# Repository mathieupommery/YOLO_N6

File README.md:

# Edge AI Vision Board (STM32N657)

This repository contains the design files for a high-performance, low-power Edge AI development board centered around the STM32N657 microcontroller. This project serves as a preliminary test platform for implementing high-speed differential and parallel buses (MIPI CSI-2 and Octo-SPI) in a compact form factor.

The primary objective is to execute YOLO-based object detection models efficiently, with data output and control interfacing managed via UART.

## Hardware Overview

### Board Images

| Front View | Back View |
| :--- | :--- |
|||

### Core Components

* **MCU:** STM32N657IO (High-performance Arm Cortex-M7 with integrated NPU)
* **External Memory (PSRAM):** 64MB Octo-SPI DTR (running at 200MHz)
* **External Storage (Flash):** 256MB Octo-SPI
    * *Note: PSRAM and Flash are multiplexed on a HyperBus and connected via a daisy-chain topology.*

### Peripherals & Connectivity

* **Camera:** MIPI CSI connector, pin-compatible with the Raspberry Pi 5 camera.
* **Display:** Integrated ST7789 SPI display.
* **Storage:** MicroSD card connector, supporting up to 50MHz mode.
* **Debug:** Dedicated debug connector.
* **Data & Power:** USB-C connector.
* **Communication:** UART connector.

## Design Details & Constraints

This design was simulated using IBIS models to ensure signal integrity across all high-speed interfaces.

### Signal Integrity Metrics

* **MIPI CSI-2:**
    * Inter-pair skew: Matched to ±30ps.
    * Intra-pair skew: Matched to <0.1ps.
* **Octo-SPI:**
    * MCU to PSRAM : 8ps skew tolerance.
    * MCU to Flash : 70ps skew tolerance.
* **Layout:** The "3H rule" was strictly implemented throughout the entire board layout, including between meandering differential pairs, to minimize crosstalk.

## Project Roadmap

This project is a stepping stone towards developing more complex hardware. Following successful verification of this prototype, the next iteration is planned to feature LPDDR4 memory integrated with an STM32MP257F MPU in a similar form factor.

---

**Contact:** [Pommery Mathieu]

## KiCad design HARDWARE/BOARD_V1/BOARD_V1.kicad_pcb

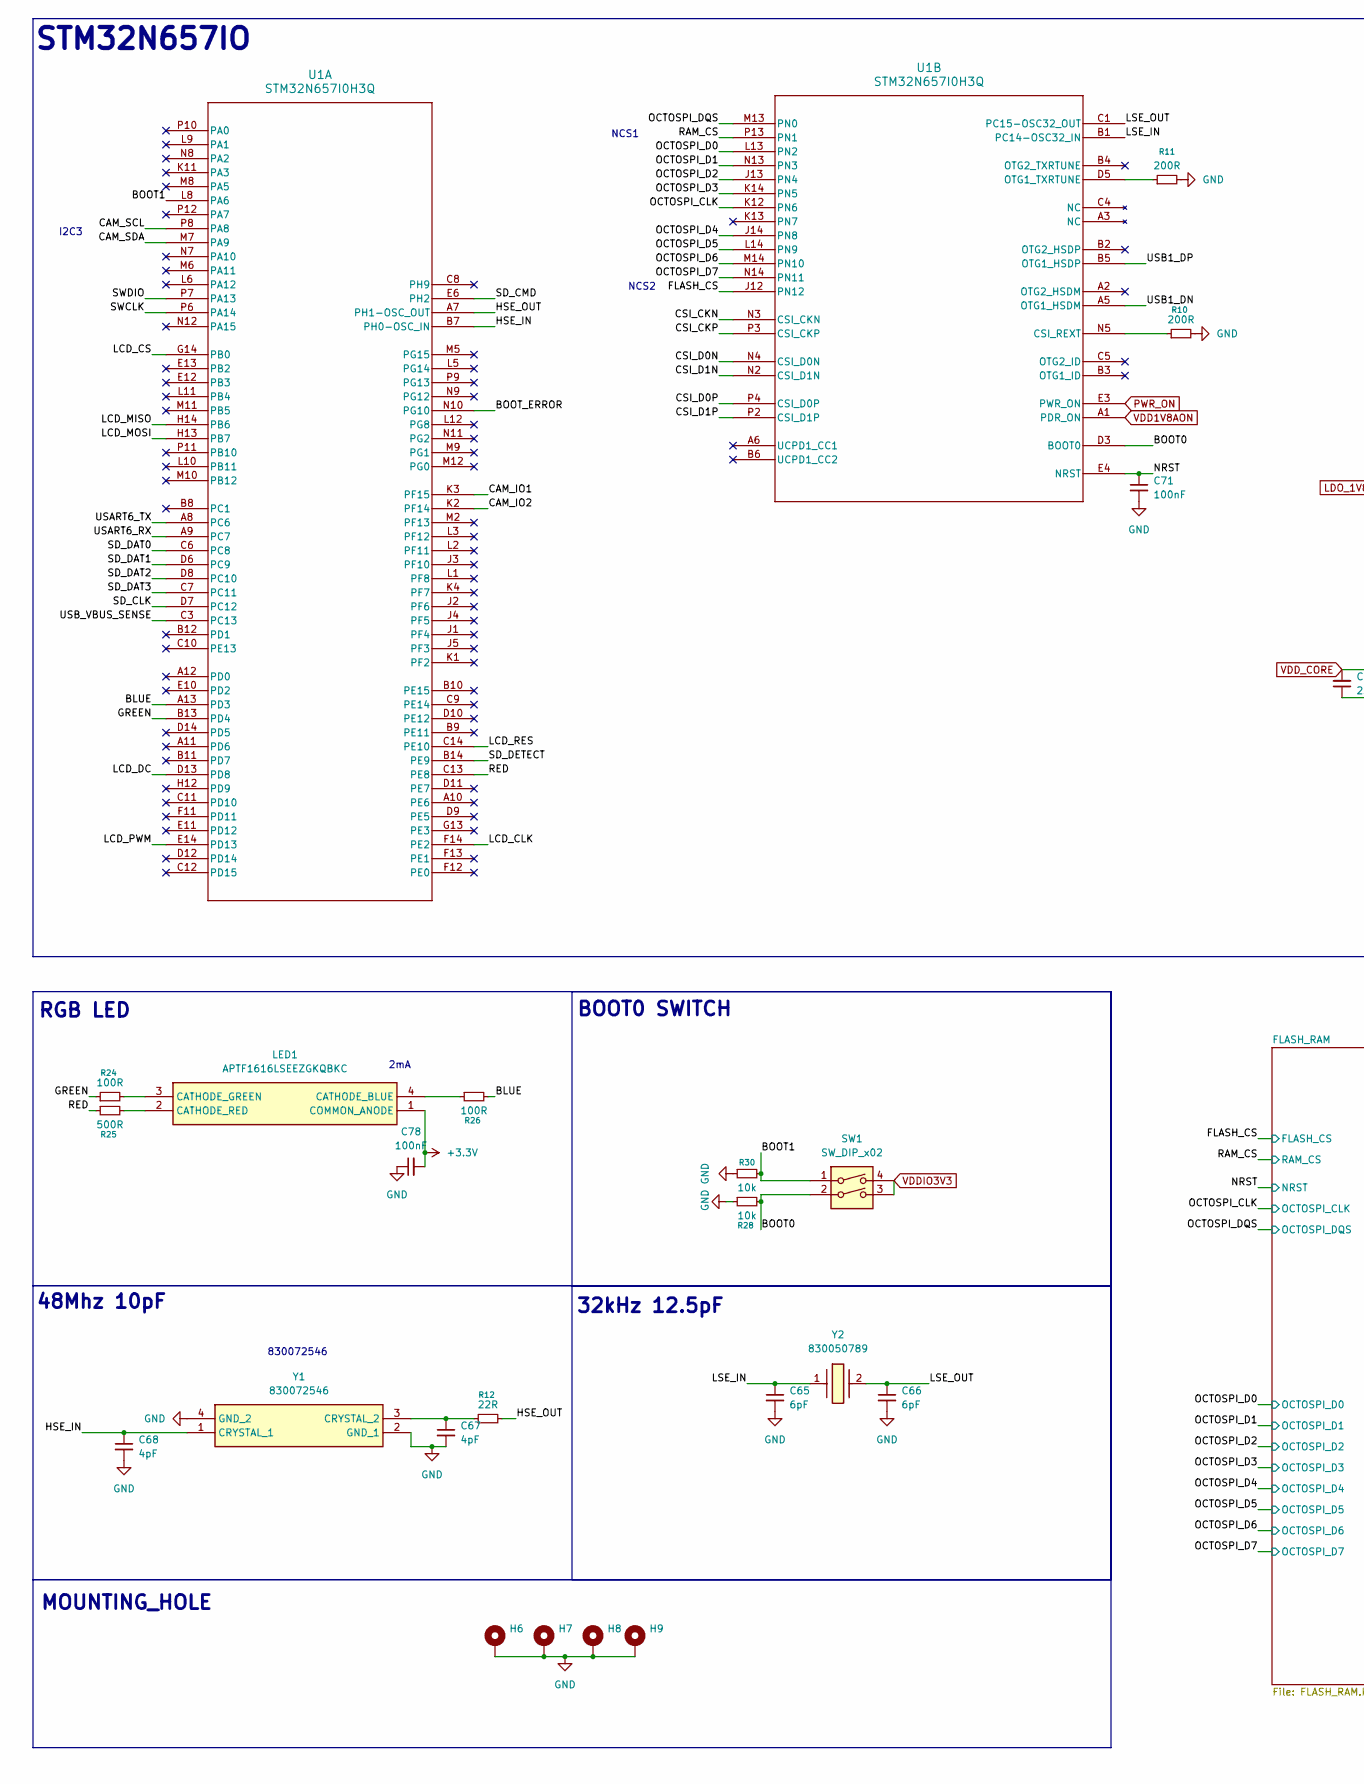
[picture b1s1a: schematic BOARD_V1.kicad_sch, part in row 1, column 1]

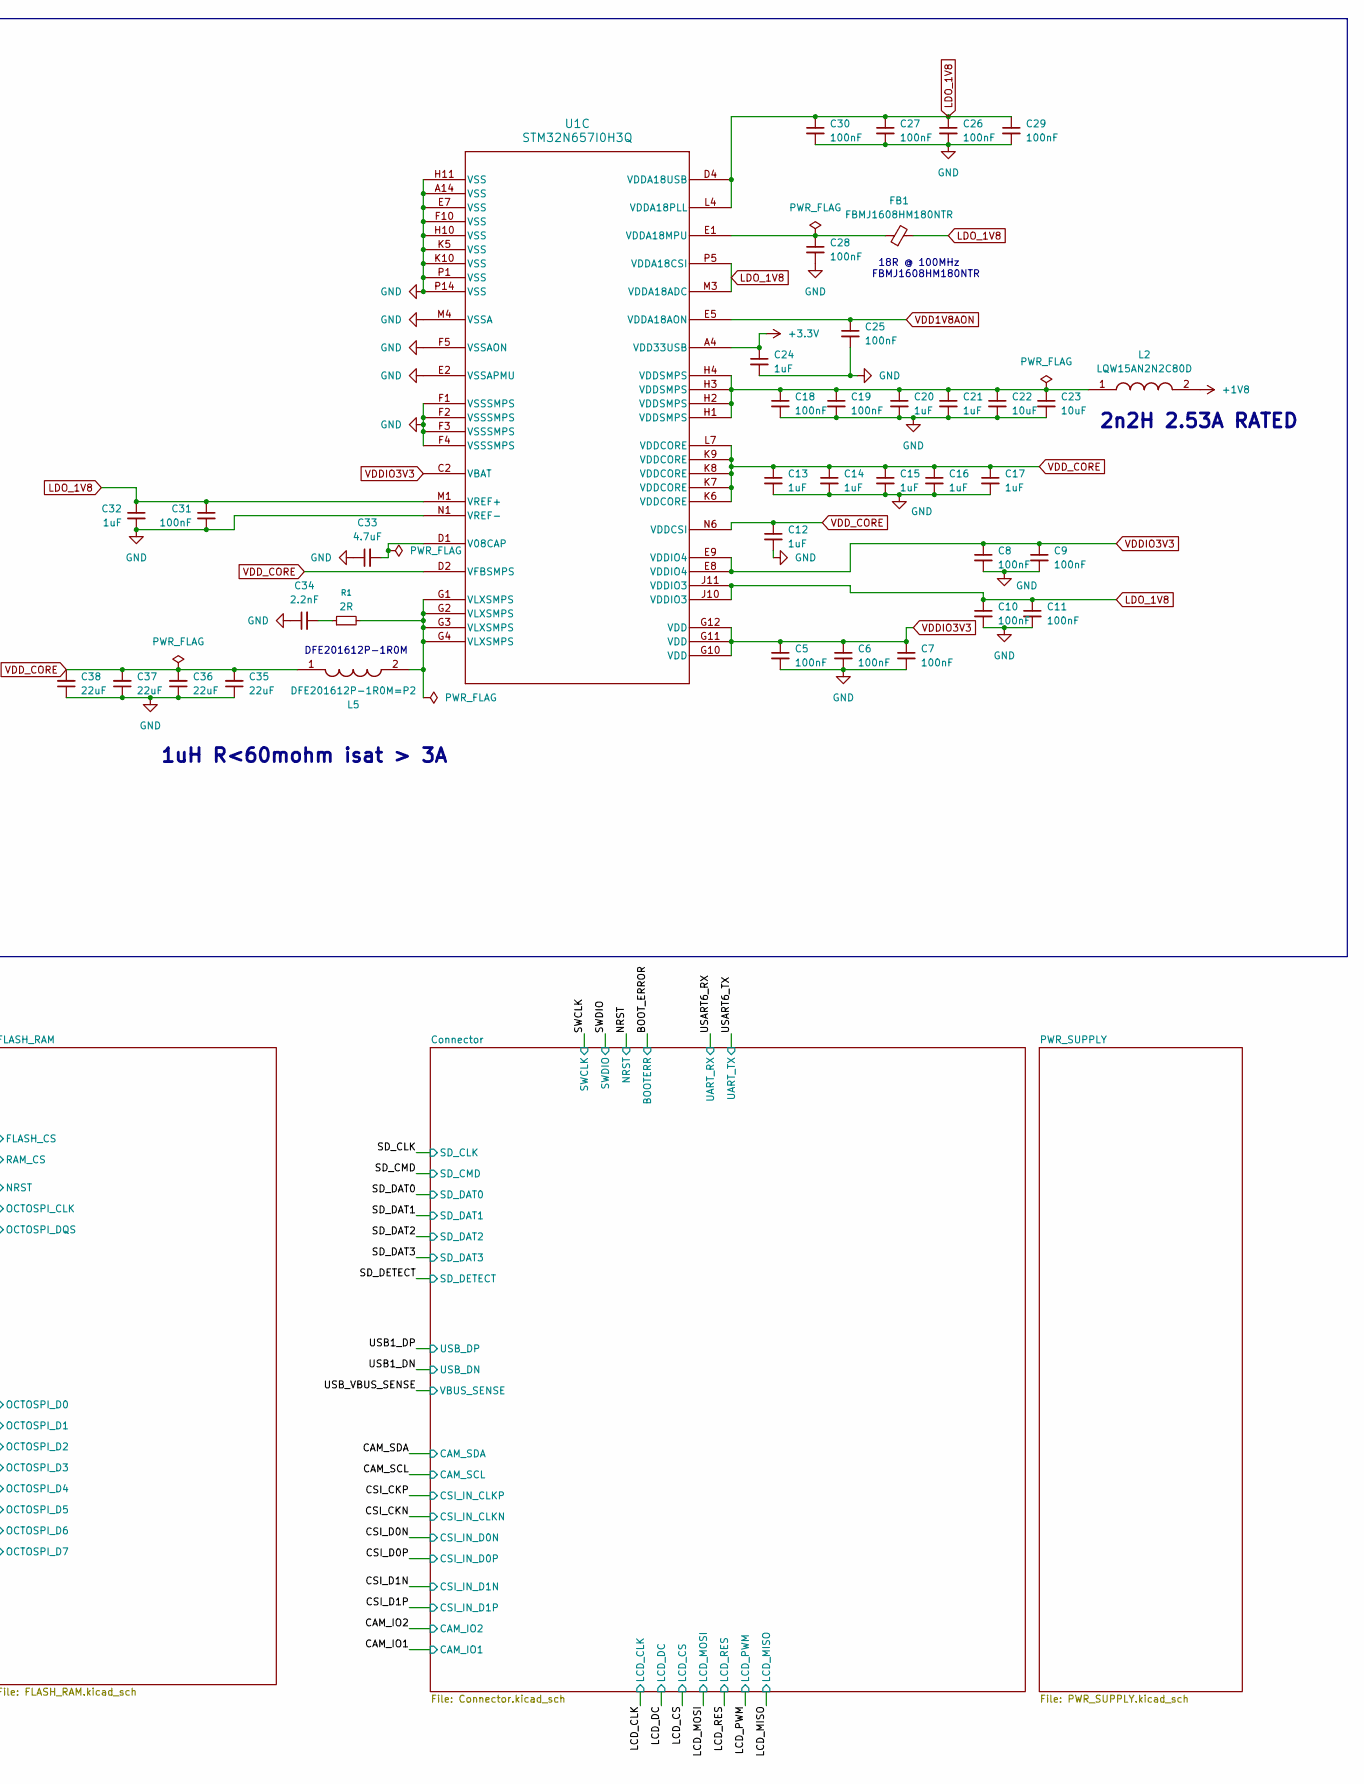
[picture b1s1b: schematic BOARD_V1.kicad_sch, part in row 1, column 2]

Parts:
C5, C6, C7, C8, C9, C10, C11, C18, C19, C25, C26, C27, C28, C29, C30, C31, C71, C78: 100nF; C_0201_0603Metric_Pad0.64x0.40mm_HandSolder
C12, C13, C14, C15, C16, C17, C20, C21, C24, C32: 1uF; C_0201_0603Metric_Pad0.64x0.40mm_HandSolder
C22, C23: 10uF; C_0402_1005Metric_Pad0.74x0.62mm_HandSolder
C33: 4.7uF; C_0402_1005Metric_Pad0.74x0.62mm_HandSolder
C34: 2.2nF; C_0201_0603Metric_Pad0.64x0.40mm_HandSolder
C35, C36, C37, C38: 22uF; C_0402_1005Metric_Pad0.74x0.62mm_HandSolder
C65, C66: 6pF; C_0201_0603Metric_Pad0.64x0.40mm_HandSolder
C67, C68: 4pF; C_0201_0603Metric_Pad0.64x0.40mm_HandSolder
FB1: FBMJ1608HM180NTR; BEADC1608X100N; Mouser Part Number 963-FBMJ1608HM180NTR
H6, H7, H8, H9: MountingHole_Pad_MP; MountingHole_2.2mm_M2_Pad_Via
L2: LQW15AN2N2C80D; LQW15AN10NG80D; Manufacturer_Part_Number LQW15AN2N2C80D; Mouser Part Number 81-LQW15AN2N2C80D
L5: DFE201612P-1R0M=P2; 1286ASH1R0MP2; Manufacturer_Part_Number DFE201612P-1R0M=P2; Mouser Part Number 81-DFE201612P-1R0MP2
LED1: APTF1616LSEEZGKQBKC; APTF1616SEEZGQBDC; Manufacturer_Part_Number APTF1616LSEEZGKQBKC; Mouser Part Number 604-APTF1616LSEEZGKQ
R1: 2R; R_0201_0603Metric_Pad0.64x0.40mm_HandSolder
R10, R11: 200R; R_0201_0603Metric_Pad0.64x0.40mm_HandSolder
R12: 22R; R_0201_0603Metric_Pad0.64x0.40mm_HandSolder
R24, R26: 100R; R_0201_0603Metric_Pad0.64x0.40mm_HandSolder
R25: 500R; R_0201_0603Metric_Pad0.64x0.40mm_HandSolder
R28, R30: 10k; R_0201_0603Metric_Pad0.64x0.40mm_HandSolder
SW1: SW_DIP_x02; SW_DIP_SPSTx02_Slide_KingTek_DSHP02TJ_W5.25mm_P1.27mm_JPin
U1: STM32N657I0H3Q; VFBGA178_12X12_STM
Y1: 830072546; Manufacturer_Part_Number 830072546; Mouser Part Number 710-830072546
Y2: 830050789; Manufacturer_Part_Number 830050789; Mouser Part Number 710-830050789

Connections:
+1V8: L2.2; also elsewhere on the board
+3.3V: C24.1, C78.2, LED1.1 (COMMON_ANODE), U1.A4 (VDD33USB); also elsewhere on the board
/BLUE: R26.2, U1.A13 (PD3)
/BOOT0: R28.2, SW1.2, U1.D3 (BOOT0)
/BOOT1: R30.2, SW1.1, U1.L8 (PA6)
/BOOT_ERROR: U1.N10 (PG10); also elsewhere on the board
/CAM_IO1: U1.K3 (PF15); also elsewhere on the board
/CAM_IO2: U1.K2 (PF14); also elsewhere on the board
/CAM_SCL: U1.P8 (PA8); also elsewhere on the board
/CAM_SDA: U1.M7 (PA9); also elsewhere on the board
/CSI_CKN: U1.N3 (CSI_CKN); also elsewhere on the board
/CSI_CKP: U1.P3 (CSI_CKP); also elsewhere on the board
/CSI_D0N: U1.N4 (CSI_D0N); also elsewhere on the board
/CSI_D0P: U1.P4 (CSI_D0P); also elsewhere on the board
/CSI_D1N: U1.N2 (CSI_D1N); also elsewhere on the board
/CSI_D1P: U1.P2 (CSI_D1P); also elsewhere on the board
/FLASH_CS: U1.J12 (PN12); also elsewhere on the board
/GREEN: R24.1, U1.B13 (PD4)
/HSE_IN: C68.1, U1.B7 (PH0-OSC_IN), Y1.1 (CRYSTAL_1)
/HSE_OUT: R12.2, U1.A7 (PH1-OSC_OUT)
/LCD_CLK: U1.F14 (PE2); also elsewhere on the board
/LCD_CS: U1.G14 (PB0); also elsewhere on the board
/LCD_DC: U1.D13 (PD8); also elsewhere on the board
/LCD_MISO: U1.H14 (PB6); also elsewhere on the board
/LCD_MOSI: U1.H13 (PB7); also elsewhere on the board
/LCD_PWM: U1.E14 (PD13); also elsewhere on the board
/LCD_RES: U1.C14 (PE10); also elsewhere on the board
/LSE_IN: C65.1, U1.B1 (PC14-OSC32_IN), Y2.1
/LSE_OUT: C66.1, U1.C1 (PC15-OSC32_OUT), Y2.2
/NRST: C71.1, U1.E4 (NRST); also elsewhere on the board
/OCTOSPI_CLK: U1.K12 (PN6); also elsewhere on the board
/OCTOSPI_D0: U1.L13 (PN2); also elsewhere on the board
/OCTOSPI_D1: U1.N13 (PN3); also elsewhere on the board
/OCTOSPI_D2: U1.J13 (PN4); also elsewhere on the board
/OCTOSPI_D3: U1.K14 (PN5); also elsewhere on the board
/OCTOSPI_D4: U1.J14 (PN8); also elsewhere on the board
/OCTOSPI_D5: U1.L14 (PN9); also elsewhere on the board
/OCTOSPI_D6: U1.M14 (PN10); also elsewhere on the board
/OCTOSPI_D7: U1.N14 (PN11); also elsewhere on the board
/OCTOSPI_DQS: U1.M13 (PN0); also elsewhere on the board
/RAM_CS: U1.P13 (PN1); also elsewhere on the board
/RED: R25.1, U1.C13 (PE8)
/SD_CLK: U1.D7 (PC12); also elsewhere on the board
/SD_CMD: U1.E6 (PH2); also elsewhere on the board
/SD_DAT0: U1.C6 (PC8); also elsewhere on the board
/SD_DAT1: U1.D6 (PC9); also elsewhere on the board
/SD_DAT2: U1.D8 (PC10); also elsewhere on the board
/SD_DAT3: U1.C7 (PC11); also elsewhere on the board
/SD_DETECT: U1.B14 (PE9); also elsewhere on the board
/SWCLK: U1.P6 (PA14); also elsewhere on the board
/SWDIO: U1.P7 (PA13); also elsewhere on the board
/USART6_RX: U1.A9 (PC7); also elsewhere on the board
/USART6_TX: U1.A8 (PC6); also elsewhere on the board
/USB1_DN: U1.A5 (OTG1_HSDM); also elsewhere on the board
/USB1_DP: U1.B5 (OTG1_HSDP); also elsewhere on the board
/USB_VBUS_SENSE: U1.C3 (PC13); also elsewhere on the board
GND: C5.2, C6.2, C7.2, C8.2, C9.2, C10.2, C11.2, C12.2, C13.2, C14.2, C15.2, C16.2, C17.2, C18.2, C19.2, C20.2, C21.2, C22.2, C23.2, C24.2, C25.2, C26.2, C27.2, C28.2, C29.2, C30.2, C31.2, C32.2, C33.1, C34.1, C35.1, C36.1, C37.1, C38.1, C65.2, C66.2, C67.2, C68.2, C71.2, C78.1, H6.1 (1_1), H7.1 (1_1), H8.1 (1_1), H9.1 (1_1), R10.2, R11.2, R28.1, R30.1, U1.A14 (VSS), U1.E2 (VSSAPMU), U1.E7 (VSS), U1.F1 (VSSSMPS), U1.F2 (VSSSMPS), U1.F3 (VSSSMPS), U1.F4 (VSSSMPS), U1.F5 (VSSAON), U1.F10 (VSS), U1.H10 (VSS), U1.H11 (VSS), U1.K5 (VSS), U1.K10 (VSS), U1.M4 (VSSA), U1.N1 (VREF-), U1.P1 (VSS), U1.P14 (VSS), Y1.2 (GND_1), Y1.4 (GND_2); also elsewhere on the board
LDO_1V8: C10.1, C11.1, C26.1, C27.1, C29.1, C30.1, C31.1, C32.1, FB1.2, U1.D4 (VDDA18USB), U1.J10 (VDDIO3), U1.J11 (VDDIO3), U1.L4 (VDDA18PLL), U1.M1 (VREF+), U1.M3 (VDDA18ADC), U1.P5 (VDDA18CSI); also elsewhere on the board
unnamed: C18.1, C19.1, C20.1, C21.1, C22.1, C23.1, L2.1, U1.H1 (VDDSMPS), U1.H2 (VDDSMPS), U1.H3 (VDDSMPS), U1.H4 (VDDSMPS)
unnamed: C34.2, R1.1
unnamed: L5.2, R1.2, U1.G1 (VLXSMPS), U1.G2 (VLXSMPS), U1.G3 (VLXSMPS), U1.G4 (VLXSMPS)
unnamed: LED1.4 (CATHODE_BLUE), R26.1
unnamed: LED1.3 (CATHODE_GREEN), R24.2
unnamed: LED1.2 (CATHODE_RED), R25.2
unnamed: R10.1, U1.N5 (CSI_REXT)
unnamed: R11.1, U1.D5 (OTG1_TXRTUNE)
unnamed: C33.2, U1.D1 (V08CAP)
unnamed: C28.1, FB1.1, U1.E1 (VDDA18MPU)
unnamed: C67.1, R12.1, Y1.3 (CRYSTAL_2)
PWR_ON: U1.E3 (PWR_ON); also elsewhere on the board
VDD1V8AON: C25.1, U1.A1 (PDR_ON), U1.E5 (VDDA18AON); also elsewhere on the board
VDDIO3V3: C5.1, C6.1, C7.1, C8.1, C9.1, SW1.3, SW1.4, U1.C2 (VBAT), U1.E8 (VDDIO4), U1.E9 (VDDIO4), U1.G10 (VDD), U1.G11 (VDD), U1.G12 (VDD); also elsewhere on the board
VDD_CORE: C12.1, C13.1, C14.1, C15.1, C16.1, C17.1, C35.2, C36.2, C37.2, C38.2, L5.1, U1.D2 (VFBSMPS), U1.K6 (VDDCORE), U1.K7 (VDDCORE), U1.K8 (VDDCORE), U1.K9 (VDDCORE), U1.L7 (VDDCORE), U1.N6 (VDDCSI)

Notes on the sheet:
FBMJ1608HM180NTR
2mA
830072546
MOUNTING_HOLE
I2C3
48Mhz 10pF
1uH R<60mohm isat > 3A
RGB LED
32kHz 12.5pF
BOOT0 SWITCH
STM32N657IO
18R @ 100MHz
NCS1
DFE201612P-1R0M
NCS2
2n2H 2.53A RATED

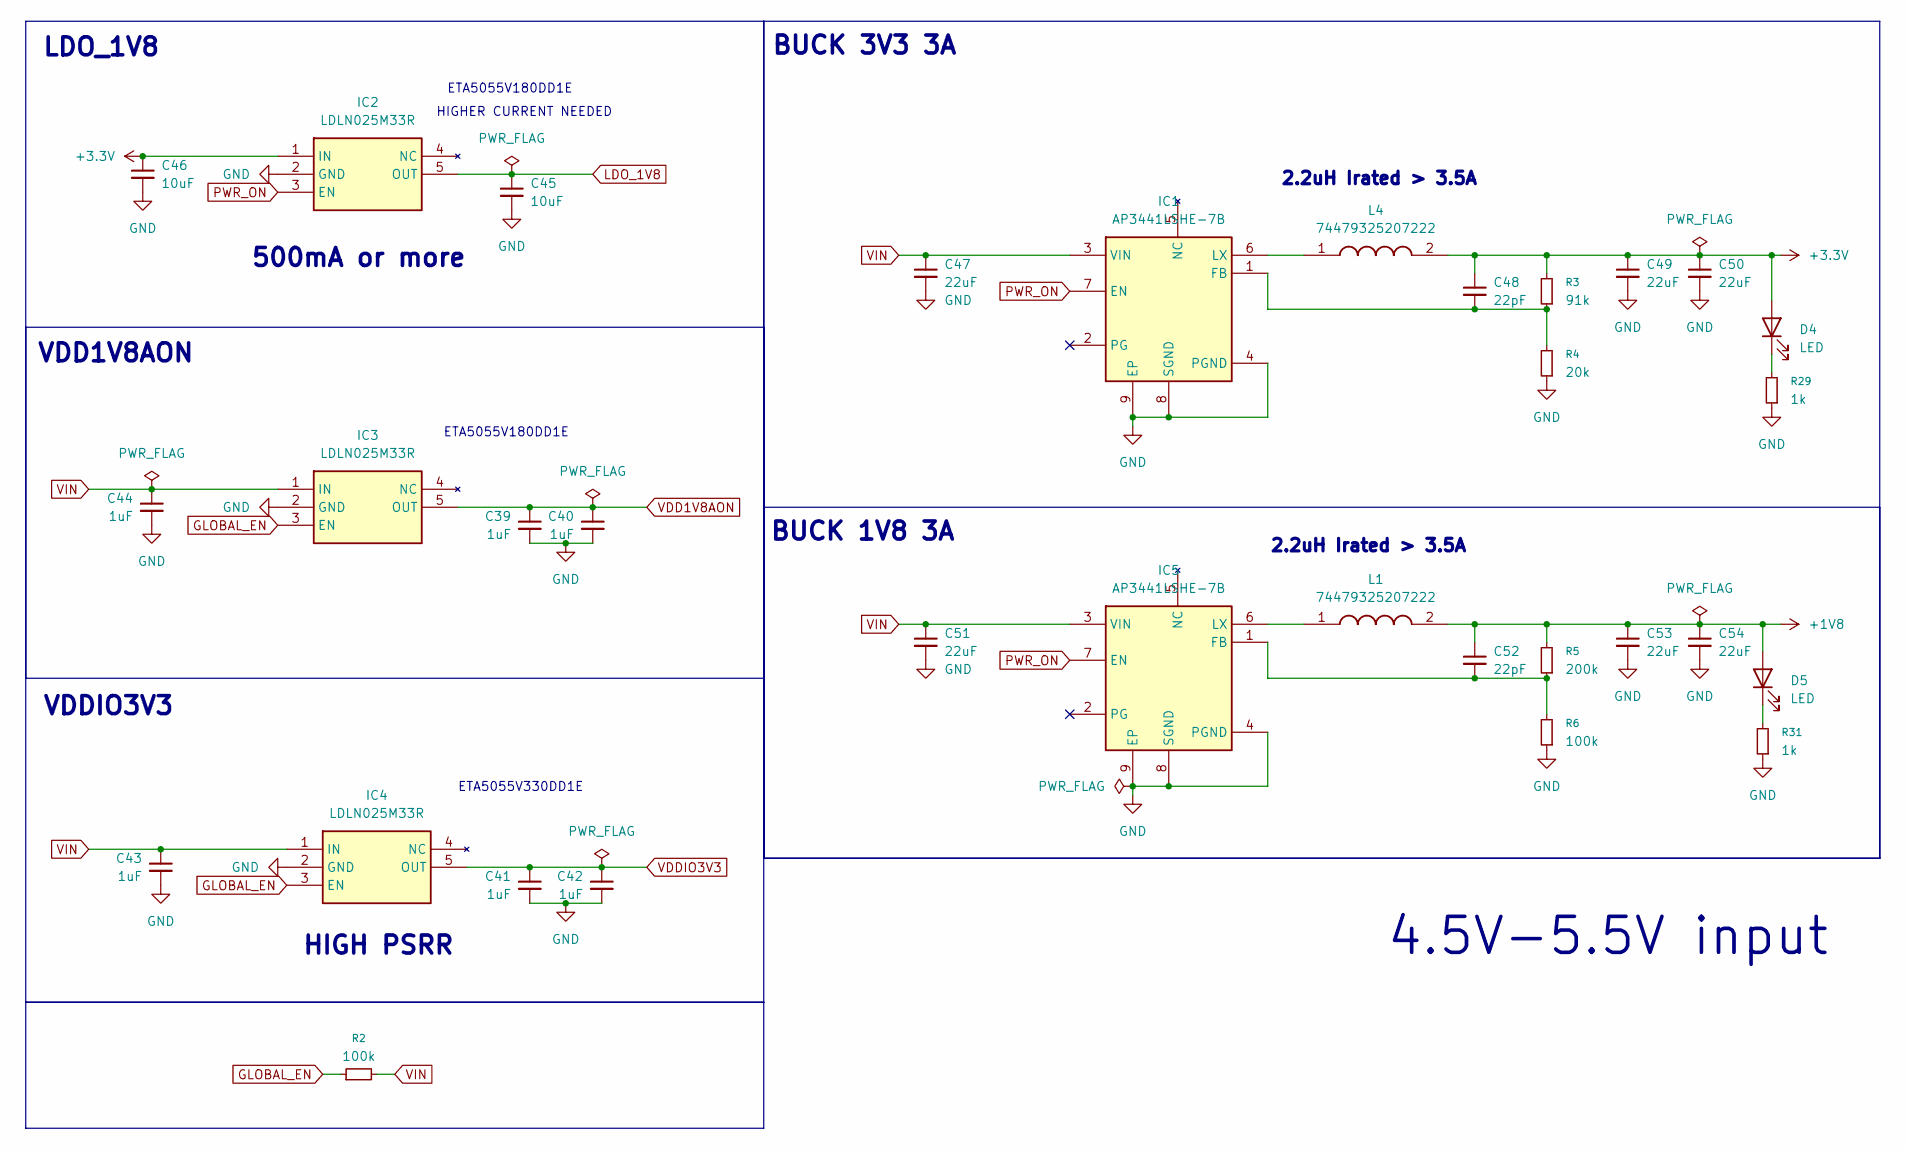
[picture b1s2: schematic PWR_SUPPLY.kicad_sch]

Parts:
C39, C40, C41, C42, C43, C44: 1uF; C_0201_0603Metric_Pad0.64x0.40mm_HandSolder
C45, C46: 10uF; C_0402_1005Metric_Pad0.74x0.62mm_HandSolder
C47, C49, C50, C51, C53, C54: 22uF; C_0603_1608Metric_Pad1.08x0.95mm_HandSolder
C48, C52: 22pF; C_0201_0603Metric_Pad0.64x0.40mm_HandSolder
D4, D5: LED; LED_0402_1005Metric
IC1, IC5: AP3441LSHE-7B; AP3441LSHE7B; Manufacturer_Part_Number AP3441LSHE-7B; Mouser Part Number 621-AP3441LSHE-7B
IC2, IC3, IC4: LDLN025M33R; SOT95P280X145-5N; Manufacturer_Part_Number LDLN025M33R; Mouser Part Number 511-LDLN025M33R 595-TLV75518PDBVR 511-L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
L1, L4: 74479325207222; Manufacturer_Part_Number 74479325207222
R2, R6: 100k; R_0201_0603Metric_Pad0.64x0.40mm_HandSolder
R3: 91k; R_0201_0603Metric_Pad0.64x0.40mm_HandSolder
R4: 20k; R_0201_0603Metric_Pad0.64x0.40mm_HandSolder
R5: 200k; R_0201_0603Metric_Pad0.64x0.40mm_HandSolder
R29, R31: 1k; R_0201_0603Metric_Pad0.64x0.40mm_HandSolder

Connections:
+1V8: C52.1, C53.1, C54.1, D5.2 (A), L1.2, R5.2; also elsewhere on the board
+3.3V: C46.1, C48.1, C49.1, C50.1, D4.2 (A), IC2.1 (IN), L4.2, R3.2; also elsewhere on the board
GLOBAL_EN: IC3.3 (EN), IC4.3 (EN), R2.1
GND: C39.2, C40.2, C41.2, C42.2, C43.2, C44.2, C45.2, C46.2, C47.2, C49.2, C50.2, C51.2, C53.2, C54.2, IC1.4 (PGND), IC1.8 (SGND), IC1.9 (EP), IC2.2 (GND), IC3.2 (GND), IC4.2 (GND), IC5.4 (PGND), IC5.8 (SGND), IC5.9 (EP), R4.1, R6.1, R29.1, R31.1; also elsewhere on the board
LDO_1V8: C45.1, IC2.5 (OUT); also elsewhere on the board
unnamed: D4.1 (K), R29.2
unnamed: D5.1 (K), R31.2
unnamed: C48.2, IC1.1 (FB), R3.1, R4.2
unnamed: IC1.6 (LX), L4.1
unnamed: C52.2, IC5.1 (FB), R5.1, R6.2
unnamed: IC5.6 (LX), L1.1
PWR_ON: IC1.7 (EN), IC2.3 (EN), IC5.7 (EN); also elsewhere on the board
VDD1V8AON: C39.1, C40.1, IC3.5 (OUT); also elsewhere on the board
VDDIO3V3: C41.1, C42.1, IC4.5 (OUT); also elsewhere on the board
VIN: C43.1, C44.1, C47.1, C51.1, IC1.3 (VIN), IC3.1 (IN), IC4.1 (IN), IC5.3 (VIN), R2.2; also elsewhere on the board

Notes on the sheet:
2.2uH Irated > 3.5A
BUCK 1V8 3A
4.5V-5.5V input
LDO_1V8
HIGH PSRR
BUCK 3V3 3A
ETA5055V180DD1E
ETA5055V330DD1E
VDDIO3V3
VDD1V8AON
HIGHER CURRENT NEEDED
500mA or more

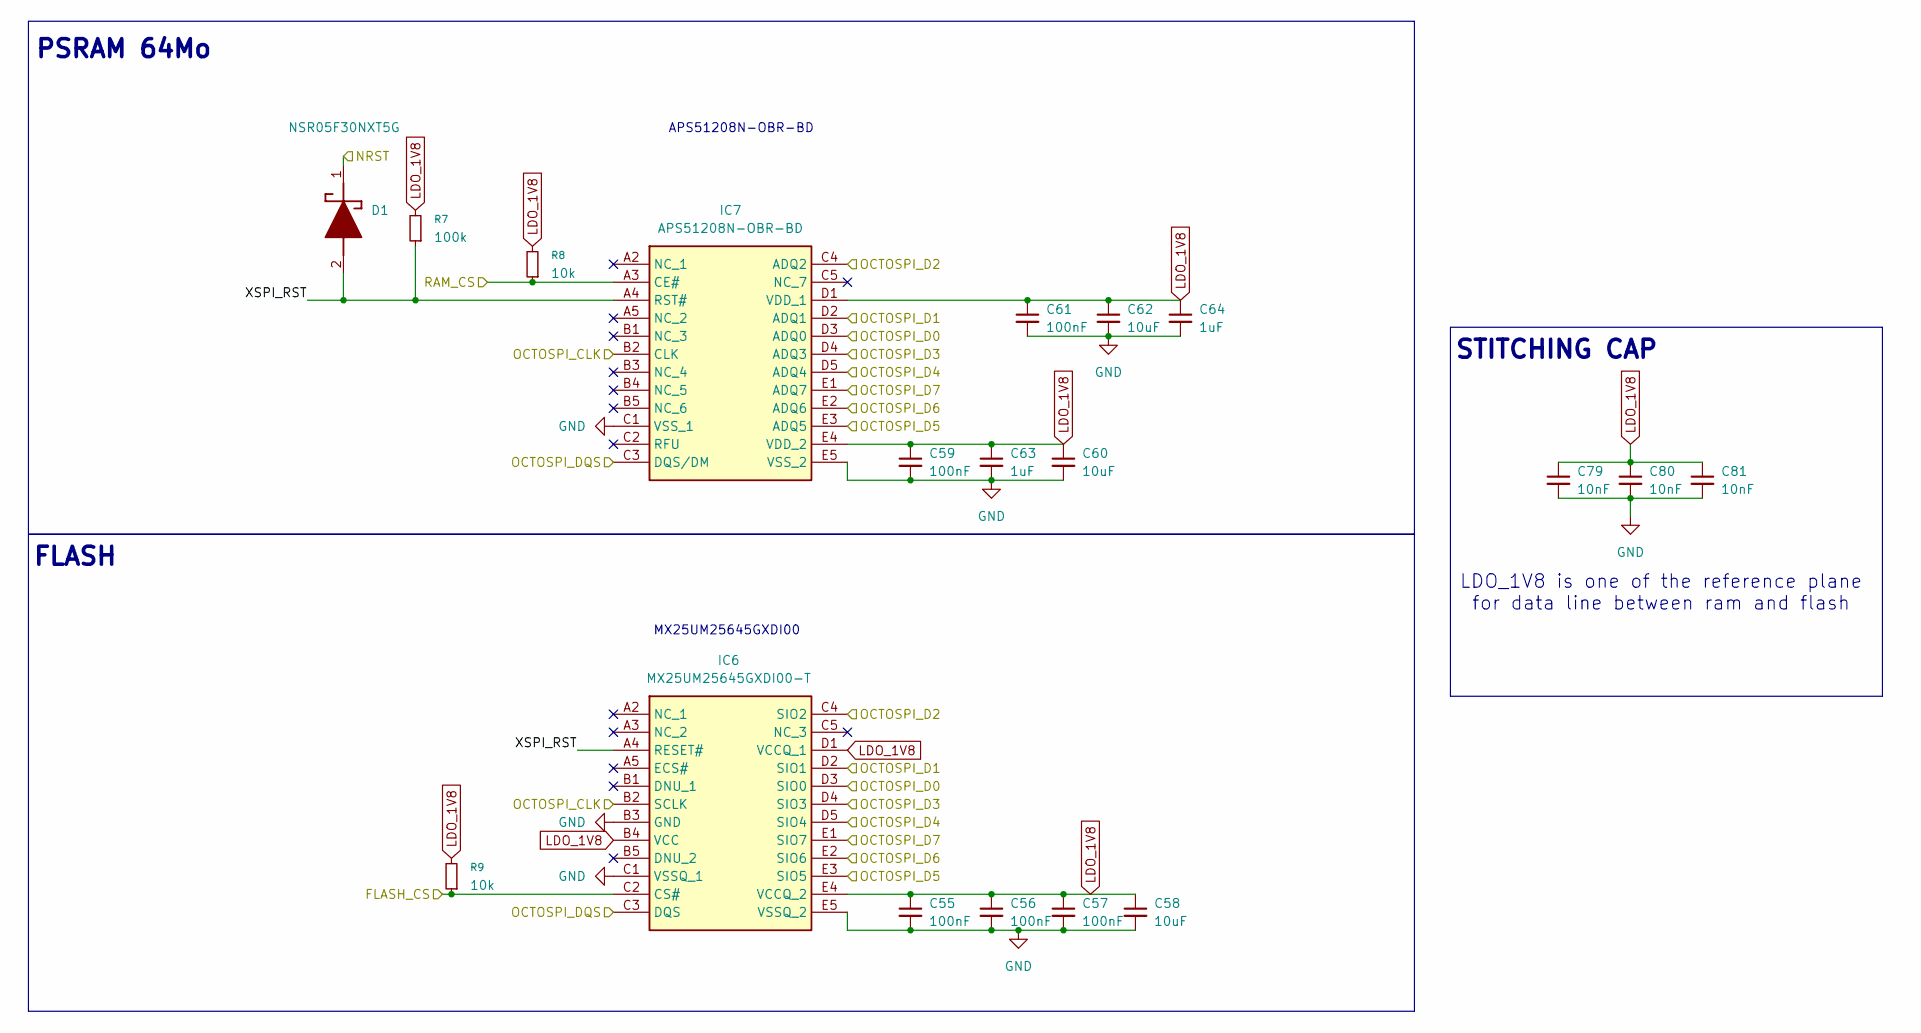
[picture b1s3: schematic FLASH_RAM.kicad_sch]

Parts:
C55, C56, C57, C59, C61: 100nF; C_0201_0603Metric_Pad0.64x0.40mm_HandSolder
C58, C60, C62: 10uF; C_0402_1005Metric_Pad0.74x0.62mm_HandSolder
C63, C64: 1uF; C_0201_0603Metric_Pad0.64x0.40mm_HandSolder
C79, C80, C81: 10nF; C_0201_0603Metric_Pad0.64x0.40mm_HandSolder
D1: NSR05F30NXT5G; Manufacturer_Part_Number NSR05F30NXT5G; Mouser Part Number 863-NSR05F30NXT5G
IC6: MX25UM25645GXDI00-T; BGA24C100P5X5_600X800X120; Manufacturer_Part_Number MX25UM25645GXDI00-T; Mouser Part Number 95-25UM25645GXDI0T
IC7: APS51208N-OBR-BD; BGA24C100P5X5_600X800X120; Manufacturer_Part_Number APS51208N-OBR-BD; Mouser Part Number 878-APS51208N-OBR-BD
R7: 100k; R_0201_0603Metric_Pad0.64x0.40mm_HandSolder
R8, R9: 10k; R_0201_0603Metric_Pad0.64x0.40mm_HandSolder

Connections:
/FLASH_CS: IC6.C2 (CS#), R9.1; also elsewhere on the board
/FLASH_RAM/XSPI_RST: D1.2 (A), IC6.A4 (RESET#), IC7.A4 (RST#), R7.1
/NRST: D1.1 (K); also elsewhere on the board
/OCTOSPI_CLK: IC6.B2 (SCLK), IC7.B2 (CLK); also elsewhere on the board
/OCTOSPI_D0: IC6.D3 (SIO0), IC7.D3 (ADQ0); also elsewhere on the board
/OCTOSPI_D1: IC6.D2 (SIO1), IC7.D2 (ADQ1); also elsewhere on the board
/OCTOSPI_D2: IC6.C4 (SIO2), IC7.C4 (ADQ2); also elsewhere on the board
/OCTOSPI_D3: IC6.D4 (SIO3), IC7.D4 (ADQ3); also elsewhere on the board
/OCTOSPI_D4: IC6.D5 (SIO4), IC7.D5 (ADQ4); also elsewhere on the board
/OCTOSPI_D5: IC6.E3 (SIO5), IC7.E3 (ADQ5); also elsewhere on the board
/OCTOSPI_D6: IC6.E2 (SIO6), IC7.E2 (ADQ6); also elsewhere on the board
/OCTOSPI_D7: IC6.E1 (SIO7), IC7.E1 (ADQ7); also elsewhere on the board
/OCTOSPI_DQS: IC6.C3 (DQS), IC7.C3 (DQS/DM); also elsewhere on the board
/RAM_CS: IC7.A3 (CE#), R8.1; also elsewhere on the board
GND: C55.2, C56.2, C57.2, C58.2, C59.2, C60.2, C61.2, C62.2, C63.2, C64.2, C79.2, C80.2, C81.2, IC6.B3 (GND), IC6.C1 (VSSQ_1), IC6.E5 (VSSQ_2), IC7.C1 (VSS_1), IC7.E5 (VSS_2); also elsewhere on the board
LDO_1V8: C55.1, C56.1, C57.1, C58.1, C59.1, C60.1, C61.1, C62.1, C63.1, C64.1, C79.1, C80.1, C81.1, IC6.B4 (VCC), IC6.D1 (VCCQ_1), IC6.E4 (VCCQ_2), IC7.D1 (VDD_1), IC7.E4 (VDD_2), R7.2, R8.2, R9.2; also elsewhere on the board

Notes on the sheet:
APS51208N-OBR-BD
PSRAM 64Mo
FLASH
STITCHING CAP
MX25UM25645GXDI00
LDO_1V8 is one of the reference plane for data line between ram and flash
